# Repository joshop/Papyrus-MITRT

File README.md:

# Papyrus Avionics System
MIT Rocket Team Liquid Propulsion Avionics

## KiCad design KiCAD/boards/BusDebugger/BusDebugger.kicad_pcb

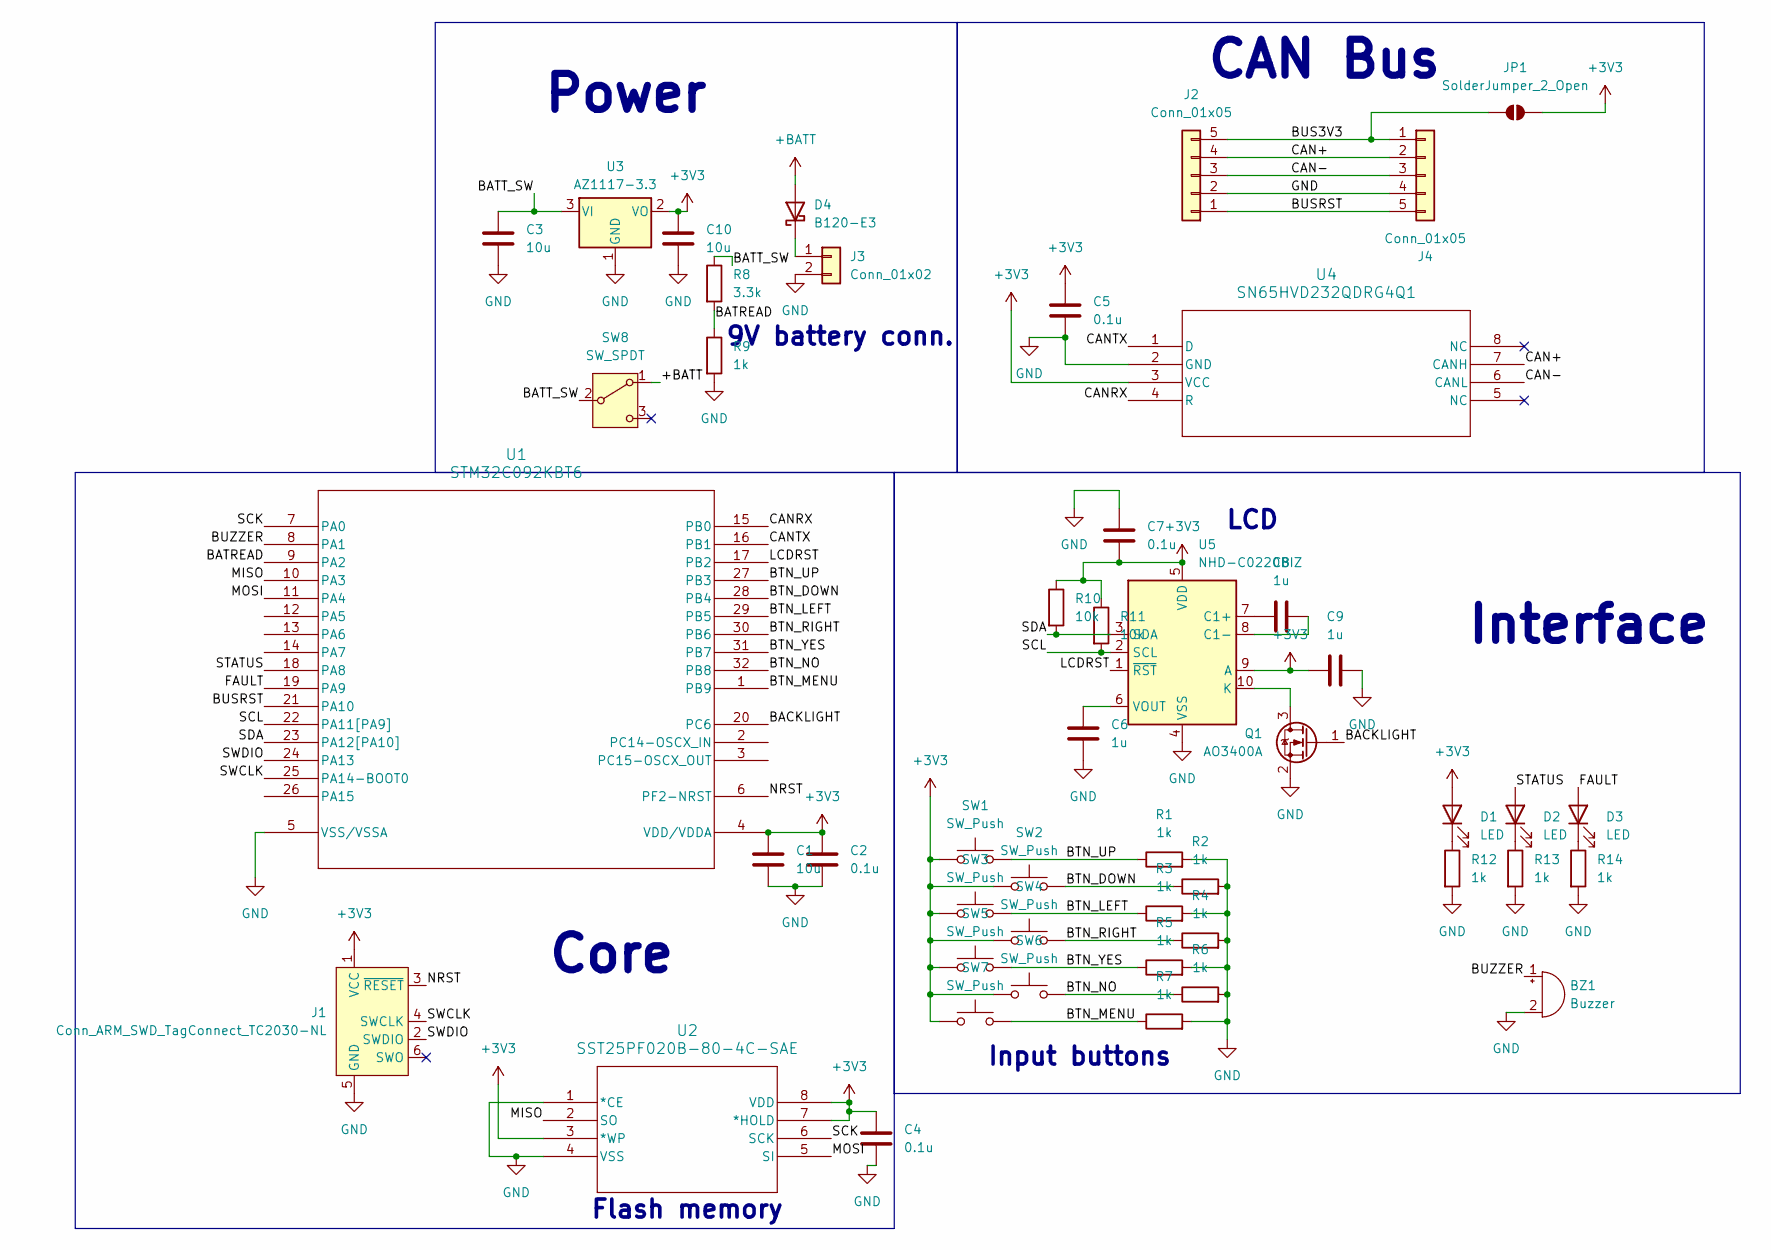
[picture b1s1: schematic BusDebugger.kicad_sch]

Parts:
BZ1: Buzzer; Buzzer_CUI_CPT-9019S-SMT
C1, C3, C10: 10u; C_0603_1608Metric
C2, C4, C5, C7: 0.1u; C_0603_1608Metric
C6, C8, C9: 1u; C_0603_1608Metric
D1, D2, D3: LED; D_0603_1608Metric
D4: B120-E3; D_SMA
J1: Conn_ARM_SWD_TagConnect_TC2030-NL; Tag-Connect_TC2030-IDC-NL_2x03_P1.27mm_Vertical
J2, J4: Conn_01x05; JST_XH_S5B-XH-A-1_1x05_P2.50mm_Horizontal
J3: Conn_01x02; PinHeader_1x02_P1.27mm_Vertical
JP1: SolderJumper_2_Open; SolderJumper-2_P1.3mm_Open_Pad1.0x1.5mm
Q1: AO3400A; SOT-23
R1, R2, R3, R4, R5, R6, R7, R9, R12, R13, R14: 1k; R_0603_1608Metric
R8: 3.3k; R_0603_1608Metric
R10, R11: 10k; R_0603_1608Metric
SW1, SW2, SW3, SW4, SW5, SW6, SW7: SW_Push; SW_Push_1P1T_NO_CK_KMR2
SW8: SW_SPDT; SW_Slide_SPDT_Straight_CK_OS102011MS2Q
U1: STM32C092KBT6; LQFP-32_STM
U2: SST25PF020B-80-4C-SAE; SOIC8_SA_SST_MCH
U3: AZ1117-3.3; SOT-223-3_TabPin2
U4: SN65HVD232QDRG4Q1; D8
U5: NHD-C0220BIZ; NHD-C0220BiZ

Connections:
+3V3: C1.1, C2.1, C4.1, C5.1, C7.2, C9.1, C10.1, D1.2 (A), J1.1 (VCC), JP1.2 (B), R10.1, R11.1, SW1.1, SW2.1, SW3.1, SW4.1, SW5.1, SW6.1, SW7.1, U1.4 (VDD/VDDA), U2.3 (*WP), U2.7 (*HOLD), U2.8 (VDD), U3.2 (VO), U4.3 (VCC), U5.5 (VDD), U5.9 (A)
+BATT: D4.2 (A), SW8.1 (A)
/BACKLIGHT: Q1.1 (G), U1.20 (PC6)
/BATREAD: R8.2, R9.1, U1.9 (PA2)
/BATT_SW: C3.1, R8.1, SW8.2 (B), U3.3 (VI)
/BTN_DOWN: R2.1, SW2.2, U1.28 (PB4)
/BTN_LEFT: R3.1, SW3.2, U1.29 (PB5)
/BTN_MENU: R7.1, SW7.2, U1.1 (PB9)
/BTN_NO: R6.1, SW6.2, U1.32 (PB8)
/BTN_RIGHT: R4.1, SW4.2, U1.30 (PB6)
/BTN_UP: R1.1, SW1.2, U1.27 (PB3)
/BTN_YES: R5.1, SW5.2, U1.31 (PB7)
/BUS3V3: J2.5, J4.1, JP1.1 (A)
/BUSRST: J2.1, J4.5, U1.21 (PA10)
/BUZZER: BZ1.1 (+), U1.8 (PA1)
/CAN+: J2.4, J4.2, U4.7 (CANH)
/CAN-: J2.3, J4.3, U4.6 (CANL)
/CANRX: U1.15 (PB0), U4.4 (R)
/CANTX: U1.16 (PB1), U4.1 (D)
/FAULT: D3.2 (A), U1.19 (PA9)
/LCDRST: U1.17 (PB2), U5.1 (~RST)
/MISO: U1.10 (PA3), U2.2 (SO)
/MOSI: U1.11 (PA4), U2.5 (SI)
/NRST: J1.3 (~RESET), U1.6 (PF2-NRST)
/SCK: U1.7 (PA0), U2.6 (SCK)
/SCL: R11.2, U1.22 (PA11[PA9]), U5.2 (SCL)
/SDA: R10.2, U1.23 (PA12[PA10]), U5.3 (SDA)
/STATUS: D2.2 (A), U1.18 (PA8)
/SWCLK: J1.4 (SWCLK), U1.25 (PA14-BOOT0)
/SWDIO: J1.2 (SWDIO), U1.24 (PA13)
GND: BZ1.2 (-), C1.2, C2.2, C3.2, C4.2, C5.2, C6.2, C7.1, C9.2, C10.2, J1.5 (GND), J2.2, J3.2, J4.4, Q1.2 (S), R1.2, R2.2, R3.2, R4.2, R5.2, R6.2, R7.2, R9.2, R12.2, R13.2, R14.2, U1.5 (VSS/VSSA), U2.1 (*CE), U2.4 (VSS), U3.1 (GND), U4.2 (GND), U5.4 (VSS)
unnamed: D1.1 (K), R12.1
unnamed: D2.1 (K), R13.1
unnamed: D3.1 (K), R14.1
unnamed: D4.1 (K), J3.1
unnamed: Q1.3 (D), U5.10 (K)
unnamed: C8.1, U5.7 (C1+)
unnamed: C8.2, U5.8 (C1-)
unnamed: C6.1, U5.6 (VOUT)

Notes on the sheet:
Core
CAN Bus
9V battery conn.
Power
Interface
LCD
Input buttons
Flash memory

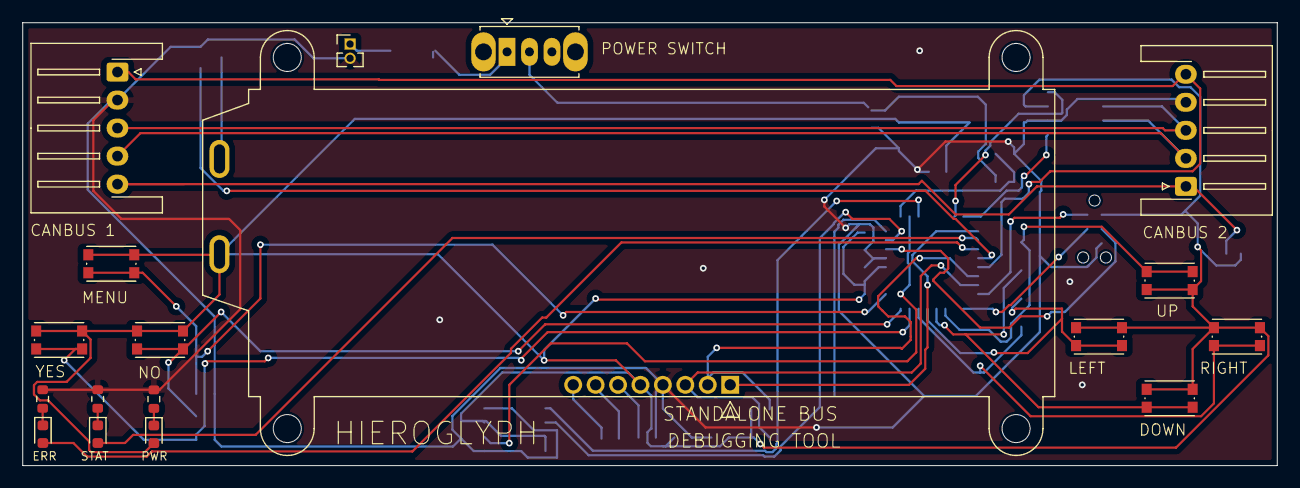
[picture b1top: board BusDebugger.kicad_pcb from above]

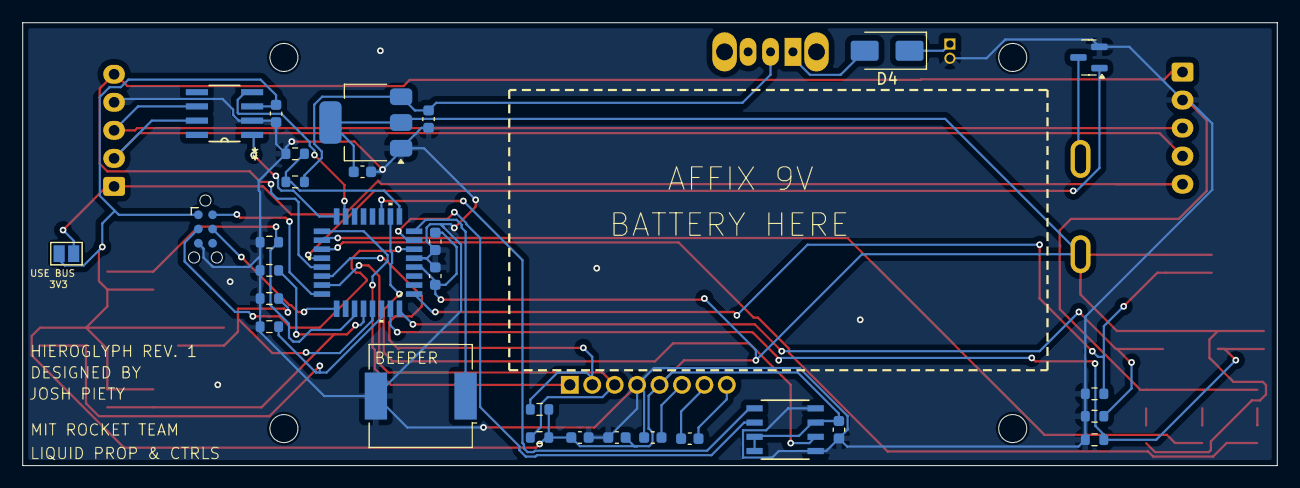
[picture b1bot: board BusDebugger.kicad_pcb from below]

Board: 2 copper layers, 111.9 x 39.5 mm, 48 parts (30 on the bottom side), 39 nets.

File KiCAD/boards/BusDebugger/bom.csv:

"Id";"Designator";"Footprint";"Quantity";"Designation";"Supplier and ref";
1;"D4";"D_SMA";1;"B120-E3";;;
2;"C10,C3,C1";"C_0603_1608Metric";3;"10u";;;
3;"J2,J4";"JST_XH_S5B-XH-A-1_1x05_P2.50mm_Horizontal";2;"Conn_01x05";;;
5;"R13,R14,R12,R3,R5,R9,R2,R4,R7,R6,R1";"R_0603_1608Metric";11;"1k";;;
6;"D1,D2,D3";"D_0603_1608Metric";3;"LED";;;
7;"SW8";"SW_Slide_SPDT_Straight_CK_OS102011MS2Q";1;"SW_SPDT";;;
8;"SW1,SW4,SW7,SW2,SW6,SW3,SW5";"SW_Push_1P1T_NO_CK_KMR2";7;"SW_Push";;;
9;"U5";"NHD-C0220BiZ";1;"NHD-C0220BIZ";;;
10;"R11,R10";"R_0603_1608Metric";2;"10k";;;
11;"C2,C4,C5,C7";"C_0603_1608Metric";4;"0.1u";;;
12;"BZ1";"Buzzer_CUI_CPT-9019S-SMT";1;"Buzzer";;;
13;"C6,C9,C8";"C_0603_1608Metric";3;"1u";;;
14;"U4";"D8";1;"SN65HVD232QDRG4Q1";;;
15;"U1";"LQFP-32_STM";1;"STM32C092KBT6";;;
16;"U3";"SOT-223-3_TabPin2";1;"AZ1117-3.3";;;
17;"R8";"R_0603_1608Metric";1;"3.3k";;;
18;"U2";"SOIC8_SA_SST_MCH";1;"SST25PF020B-80-4C-SAE";;;
19;"Q1";"SOT-23";1;"AO3400A";;;

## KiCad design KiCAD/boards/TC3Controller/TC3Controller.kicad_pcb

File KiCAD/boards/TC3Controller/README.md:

# TC3Controller
This is a controller board for three K-type thermocouples. In addition to the standard components, it contains:
- three MAX31855KASA thermocouple amplifiers
- optional filtering capacitors on thermocouple inputs
- three 2-terminal 2.54mm pitch screw terminals for thermocouples
- STATUS and FAULT LEDs
The board itself is 35.0mm x 37.3mm and uses M2 mounting holes.

We considered designing our own thermocouple amplifier to save cost, but decided not to. If necessary, this could be implemented as follows:
- Using a low noise amplifier such as the LMP7716MMX/NOPB (dual), produce a desired gain with feedback.
- Use another amplifier device, likely in the same dual package, to buffer a resistor divider and offset the voltage to allow reading of temperatures below the cold junction temperature.
- Separately, connect a temperature sensor such as the TMP126EDBVRQ1 and perform cold junction compensation in software.
Cold junction compensators and buffers could be reused between individual thermocouples.

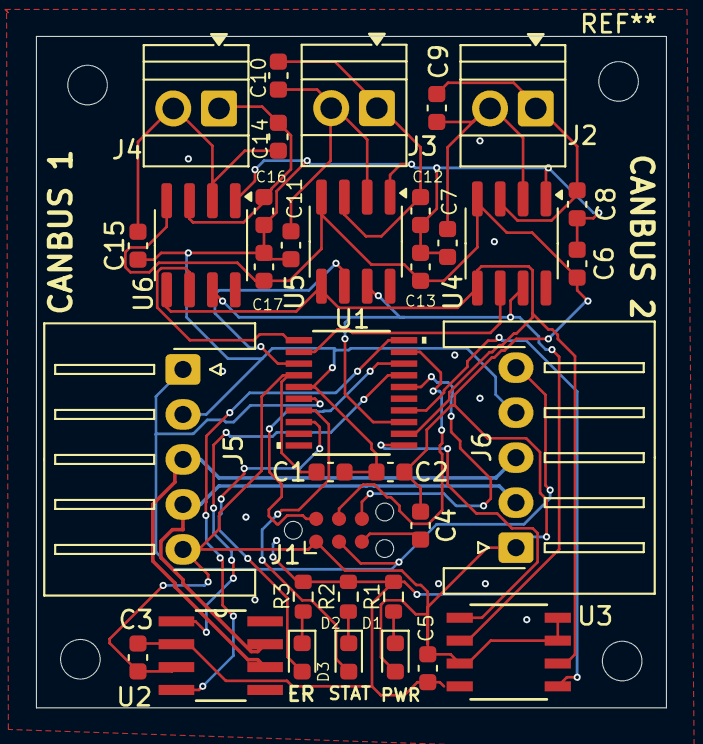
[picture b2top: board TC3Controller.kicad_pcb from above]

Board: 2 copper layers, 35.0 x 37.3 mm, 35 parts (0 on the bottom side), 28 nets.

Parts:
C1, C3, C4, C5, C6, C7, C8, C9, C10, C11, C12, C13, C14, C15, C16, C17: 100n; C_0603_1608Metric
C2: 10u; C_0603_1608Metric
D1, D2, D3: LED; LED_0603_1608Metric
J1: Conn_ARM_SWD_TagConnect_TC2030-NL; Tag-Connect_TC2030-IDC-NL_2x03_P1.27mm_Vertical
J2, J3, J4: Screw_Terminal_01x02; TerminalBlock_Xinya_XY308-2.54-2P_1x02_P2.54mm_Horizontal
J5, J6: Conn_01x05; JST_XH_S5B-XH-A-1_1x05_P2.50mm_Horizontal
R1, R2, R3: 1k; R_0603_1608Metric
U1: STM32C092FCP6; TSSOP20_STM
U2: SN65HVD232QDRG4Q1; D8
U3: SST25PF020B-80-4C-SAE; SOIC8_SA_SST_MCH
U4, U5, U6: MAX31855KASA; SOIC-8_3.9x4.9mm_P1.27mm

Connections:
+3V3: C1.1, C2.1, C3.1, C4.1, C5.1, C6.1, C13.1, C17.1, D1.2 (A), J1.1 (VCC), J5.5, J6.1, U1.4 (VDD/VDDA), U2.3 (VCC), U3.3 (*WP), U3.7 (*HOLD), U3.8 (VDD), U4.4 (V_{CC}), U5.4 (V_{CC}), U6.4 (V_{CC})
/CAN+: J5.4, J6.2, U2.7 (CANH)
/CAN-: J5.3, J6.3, U2.6 (CANL)
/CANRX: U1.20 (PB3/PB4/PB5/PB6), U2.4 (R)
/CANTX: U1.17 (PA12[PA10]), U2.1 (D)
/FAULT: D3.2 (A), U1.8 (PA1)
/FLASH_CE: U1.11 (PA4), U3.1 (*CE)
/MISO: U1.13 (PA6), U3.2 (SO), U4.7 (SO), U5.7 (SO), U6.7 (SO)
/MOSI: U1.14 (PA7), U3.5 (SI)
/RESETB: J1.3 (~RESET), J5.1, J6.5, U1.6 (PF2-NRST)
/SCK: U1.12 (PA5), U3.6 (SCK), U4.5 (SCK), U5.5 (SCK), U6.5 (SCK)
/STATUS: D2.2 (A), U1.7 (PA0)
/SWCLK: J1.4 (SWCLK), U1.19 (PA14-BOOT0/PA15)
/SWDIO: J1.2 (SWDIO), U1.18 (PA13)
/SWO: J1.6 (SWO), U1.16 (PA11[PA9])
/TC1_CS: U1.1 (PB7/PB8), U6.6 (~CS)
/TC2_CS: U1.2 (PC14-OSCX_IN), U4.6 (~CS)
/TC3_CS: U1.3 (PC15-OSCX_OUT), U5.6 (~CS)
GND: C1.2, C2.2, C3.2, C4.2, C5.2, C6.2, C7.2, C8.1, C11.2, C12.1, C13.2, C15.2, C16.1, C17.2, J1.5 (GND), J5.2, J6.4, R1.2, R2.2, R3.2, U1.5 (VSS/VSSA), U2.2 (GND), U3.4 (VSS), U4.1 (GND), U5.1 (GND), U6.1 (GND)
unnamed: D1.1 (K), R1.1
unnamed: D2.1 (K), R2.1
unnamed: D3.1 (K), R3.1
unnamed: C8.2, C9.1, J2.1, U4.3 (T+)
unnamed: C7.1, C9.2, J2.2, U4.2 (T-)
unnamed: C10.1, C12.2, J3.1, U5.3 (T+)
unnamed: C10.2, C11.1, J3.2, U5.2 (T-)
unnamed: C14.1, C16.2, J4.1, U6.3 (T+)
unnamed: C14.2, C15.1, J4.2, U6.2 (T-)

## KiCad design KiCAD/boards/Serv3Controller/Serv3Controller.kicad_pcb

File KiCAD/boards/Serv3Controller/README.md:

# Serv3Controller
This is a controller board for three servo motors. In addition to the standard components, it contains:
- three IRLML6344TRPBF N-channel MOSFETs for switching servo power
- STATUS LEDs for each servo to indicate both power and fault conditions
- two 2-terminal 2.54mm pitch screw terminals for servo voltage (5V or greater)
- 33mohm current sense resistors on each servo to detect stall conditions
- three standard 2.54mm male pin headers to connect to servos
The board itself is 42.4mm x 29.6mm and uses M2 mounting holes.

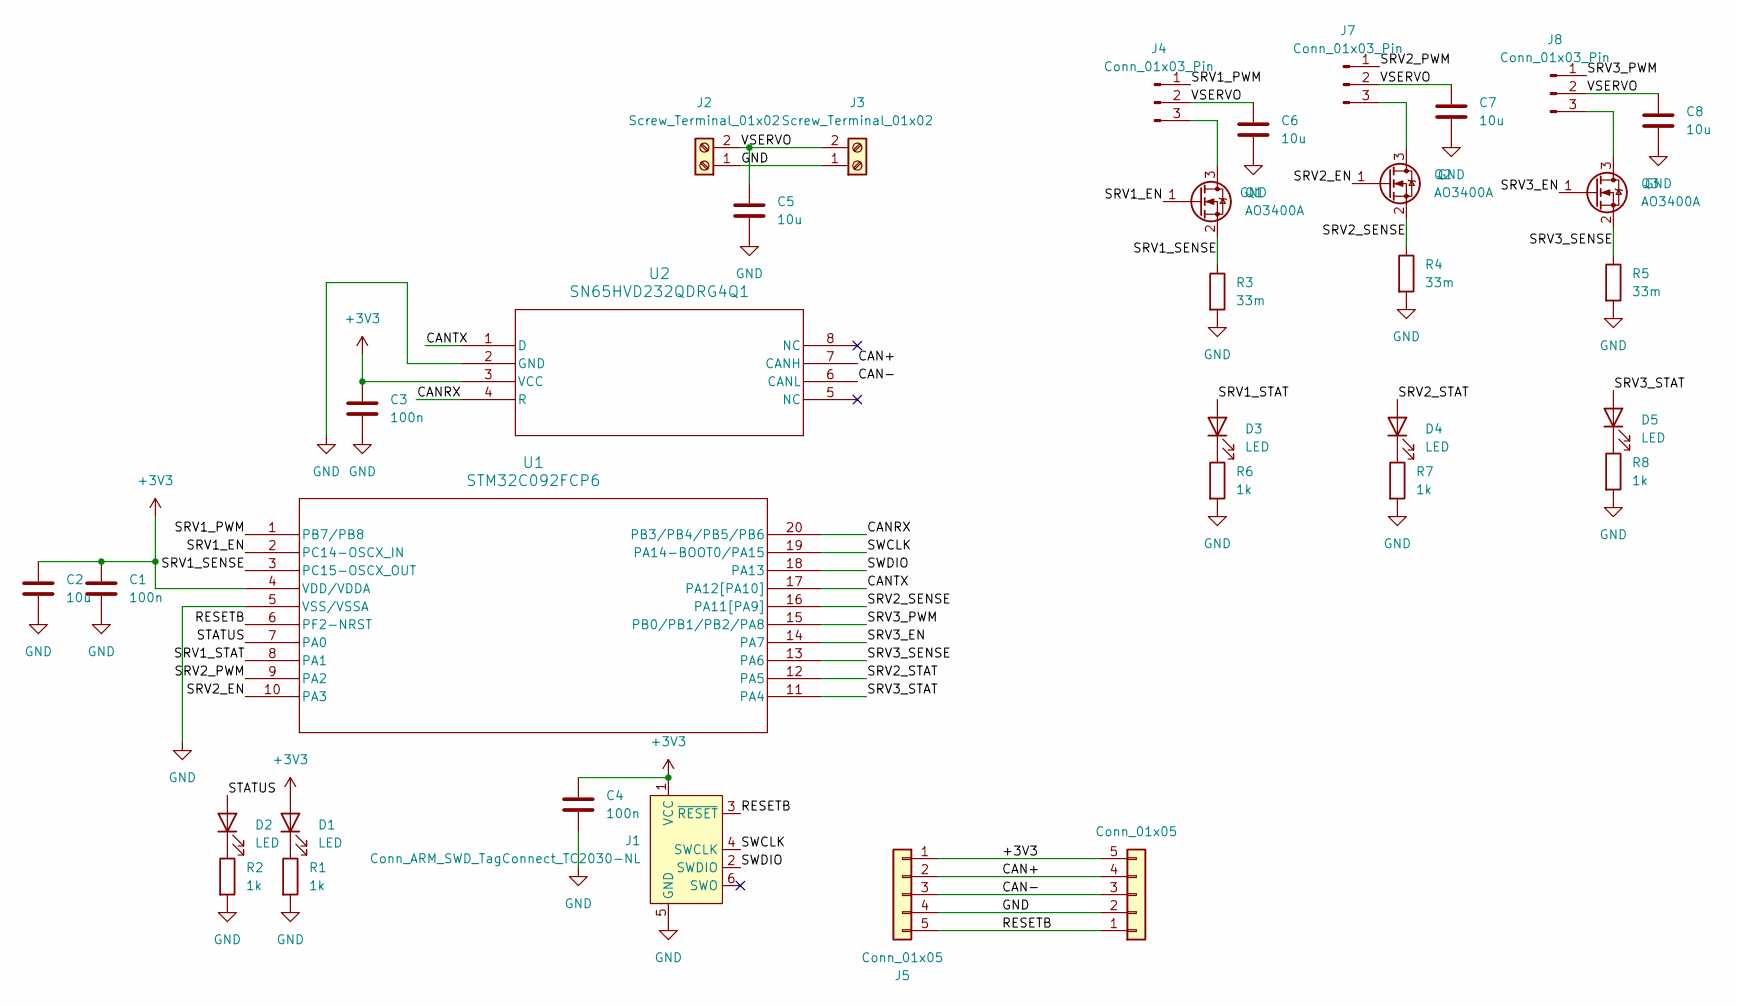
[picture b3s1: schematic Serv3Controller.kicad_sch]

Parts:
C1, C3, C4: 100n; C_0603_1608Metric
C2, C5, C6, C7, C8: 10u; C_0603_1608Metric
D1, D2, D3, D4, D5: LED; LED_0603_1608Metric
J1: Conn_ARM_SWD_TagConnect_TC2030-NL; Tag-Connect_TC2030-IDC-NL_2x03_P1.27mm_Vertical
J2, J3: Screw_Terminal_01x02; TerminalBlock_Xinya_XY308-2.54-2P_1x02_P2.54mm_Horizontal
J4, J7, J8: Conn_01x03_Pin; PinHeader_1x03_P2.54mm_Vertical
J5, J6: Conn_01x05; JST_XH_S5B-XH-A-1_1x05_P2.50mm_Horizontal
Q1, Q2, Q3: AO3400A; SOT-23
R1, R2, R6, R7, R8: 1k; R_0603_1608Metric
R3, R4, R5: 33m; R_0603_1608Metric
U1: STM32C092FCP6; TSSOP20_STM
U2: SN65HVD232QDRG4Q1; D8

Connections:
+3V3: C1.1, C2.1, C3.1, C4.1, D1.2 (A), J1.1 (VCC), J5.1, J6.5, U1.4 (VDD/VDDA), U2.3 (VCC)
/CAN+: J5.2, J6.4, U2.7 (CANH)
/CAN-: J5.3, J6.3, U2.6 (CANL)
/CANRX: U1.20 (PB3/PB4/PB5/PB6), U2.4 (R)
/CANTX: U1.17 (PA12[PA10]), U2.1 (D)
/RESETB: J1.3 (~RESET), J5.5, J6.1, U1.6 (PF2-NRST)
/SRV1_EN: Q1.1 (G), U1.2 (PC14-OSCX_IN)
/SRV1_PWM: J4.1, U1.1 (PB7/PB8)
/SRV1_SENSE: Q1.2 (S), R3.1, U1.3 (PC15-OSCX_OUT)
/SRV1_STAT: D3.2 (A), U1.8 (PA1)
/SRV2_EN: Q2.1 (G), U1.10 (PA3)
/SRV2_PWM: J7.1, U1.9 (PA2)
/SRV2_SENSE: Q2.2 (S), R4.1, U1.16 (PA11[PA9])
/SRV2_STAT: D4.2 (A), U1.12 (PA5)
/SRV3_EN: Q3.1 (G), U1.14 (PA7)
/SRV3_PWM: J8.1, U1.15 (PB0/PB1/PB2/PA8)
/SRV3_SENSE: Q3.2 (S), R5.1, U1.13 (PA6)
/SRV3_STAT: D5.2 (A), U1.11 (PA4)
/STATUS: D2.2 (A), U1.7 (PA0)
/SWCLK: J1.4 (SWCLK), U1.19 (PA14-BOOT0/PA15)
/SWDIO: J1.2 (SWDIO), U1.18 (PA13)
/VSERVO: C5.1, C6.1, C7.1, C8.1, J2.2, J3.2, J4.2, J7.2, J8.2
GND: C1.2, C2.2, C3.2, C4.2, C5.2, C6.2, C7.2, C8.2, J1.5 (GND), J2.1, J3.1, J5.4, J6.2, R1.2, R2.2, R3.2, R4.2, R5.2, R6.2, R7.2, R8.2, U1.5 (VSS/VSSA), U2.2 (GND)
unnamed: D1.1 (K), R1.1
unnamed: D2.1 (K), R2.1
unnamed: D3.1 (K), R6.1
unnamed: D4.1 (K), R7.1
unnamed: D5.1 (K), R8.1
unnamed: J4.3, Q1.3 (D)
unnamed: J7.3, Q2.3 (D)
unnamed: J8.3, Q3.3 (D)

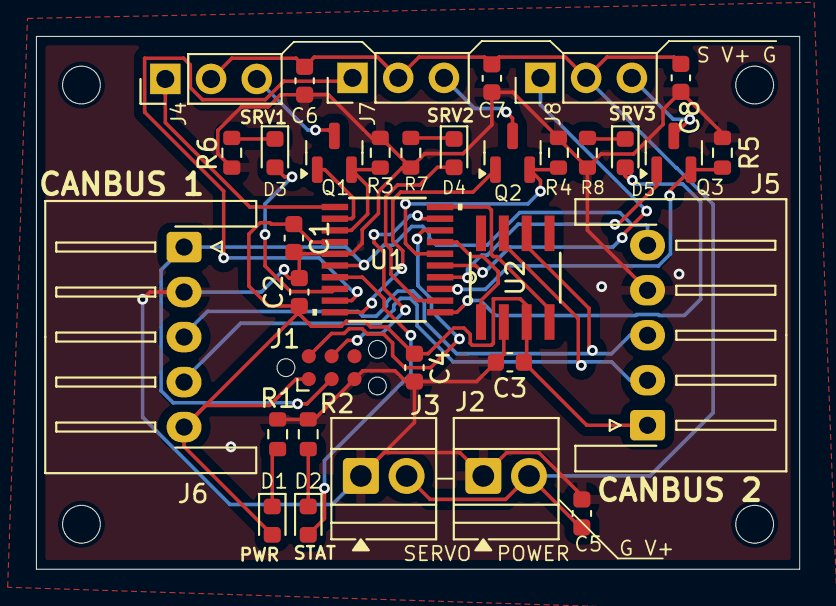
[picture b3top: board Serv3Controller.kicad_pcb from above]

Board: 2 copper layers, 42.4 x 29.6 mm, 34 parts (0 on the bottom side), 31 nets.

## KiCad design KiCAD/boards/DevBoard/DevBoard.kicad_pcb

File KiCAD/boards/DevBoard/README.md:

# DevBoard
This is a test board for STM32C092 microcontroller and CAN bus. It contains the following components, common to most/all standard boards in the DAQ system:
- STM32C092FCP6 microcontroller, TSSOP-20 package with built in FDCAN
- SN65HVD232QDRG4Q1 CAN transceiver
- SST25PF020B-80-4C-SAE SPI flash memory
- Tag-Connect 6-pin programming header through SWD
All STM32 peripheral pins and the CAN bus are broken out to headers.

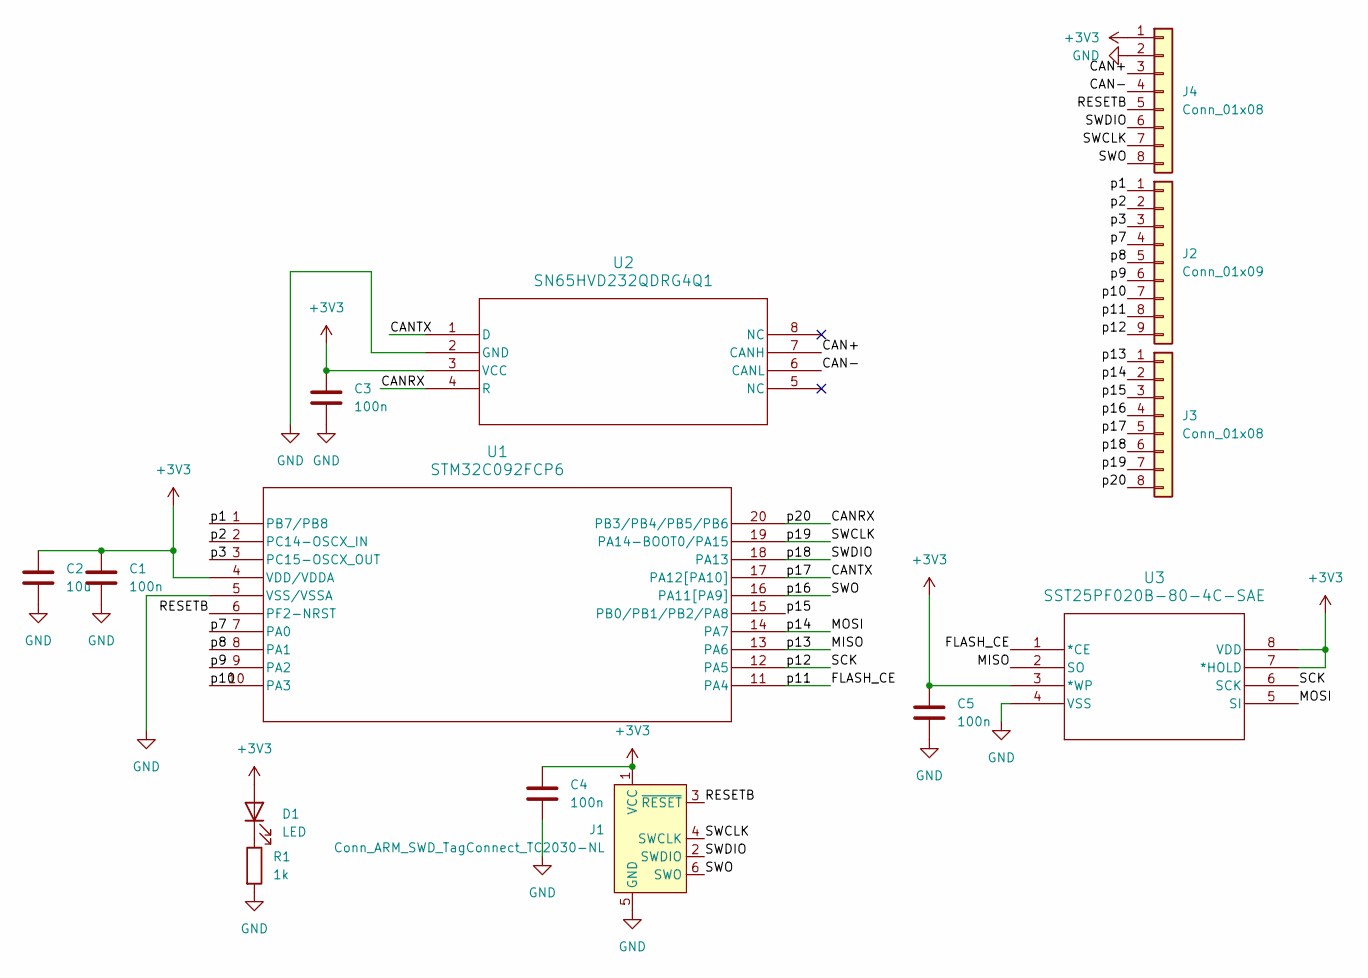
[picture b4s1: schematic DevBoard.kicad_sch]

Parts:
C1, C3, C4, C5: 100n; C_0603_1608Metric
C2: 10u; C_0603_1608Metric
D1: LED; LED_0603_1608Metric
J1: Conn_ARM_SWD_TagConnect_TC2030-NL; Tag-Connect_TC2030-IDC-NL_2x03_P1.27mm_Vertical
J2: Conn_01x09; PinSocket_1x09_P2.54mm_Vertical
J3, J4: Conn_01x08; PinSocket_1x08_P2.54mm_Vertical
R1: 1k; R_0603_1608Metric
U1: STM32C092FCP6; TSSOP20_STM
U2: SN65HVD232QDRG4Q1; D8
U3: SST25PF020B-80-4C-SAE; SOIC8_SA_SST_MCH

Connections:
+3V3: C1.1, C2.1, C3.1, C4.1, C5.1, D1.2 (A), J1.1 (VCC), J4.1, U1.4 (VDD/VDDA), U2.3 (VCC), U3.3 (*WP), U3.7 (*HOLD), U3.8 (VDD)
/CAN+: J4.3, U2.7 (CANH)
/CAN-: J4.4, U2.6 (CANL)
/CANRX: J3.8, U1.20 (PB3/PB4/PB5/PB6), U2.4 (R)
/CANTX: J3.5, U1.17 (PA12[PA10]), U2.1 (D)
/FLASH_CE: J2.8, U1.11 (PA4), U3.1 (*CE)
/MISO: J3.1, U1.13 (PA6), U3.2 (SO)
/MOSI: J3.2, U1.14 (PA7), U3.5 (SI)
/RESETB: J1.3 (~RESET), J4.5, U1.6 (PF2-NRST)
/SCK: J2.9, U1.12 (PA5), U3.6 (SCK)
/SWCLK: J1.4 (SWCLK), J3.7, J4.7, U1.19 (PA14-BOOT0/PA15)
/SWDIO: J1.2 (SWDIO), J3.6, J4.6, U1.18 (PA13)
/SWO: J1.6 (SWO), J3.4, J4.8, U1.16 (PA11[PA9])
/p1: J2.1, U1.1 (PB7/PB8)
/p2: J2.2, U1.2 (PC14-OSCX_IN)
/p3: J2.3, U1.3 (PC15-OSCX_OUT)
/p7: J2.4, U1.7 (PA0)
/p8: J2.5, U1.8 (PA1)
/p9: J2.6, U1.9 (PA2)
/p10: J2.7, U1.10 (PA3)
/p15: J3.3, U1.15 (PB0/PB1/PB2/PA8)
GND: C1.2, C2.2, C3.2, C4.2, C5.2, J1.5 (GND), J4.2, R1.2, U1.5 (VSS/VSSA), U2.2 (GND), U3.4 (VSS)
unnamed: D1.1 (K), R1.1

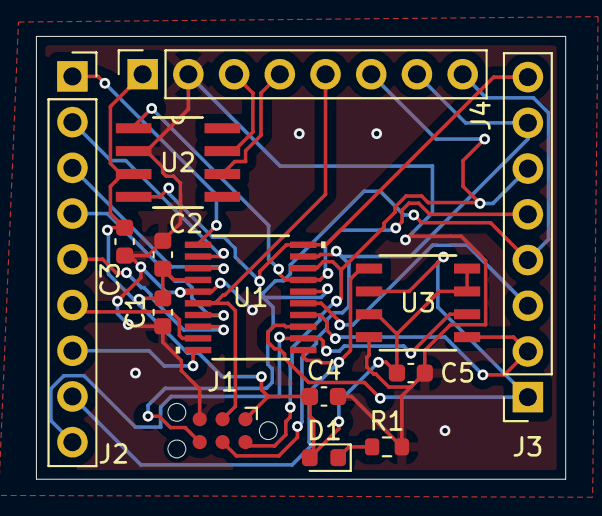
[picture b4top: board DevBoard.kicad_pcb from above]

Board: 2 copper layers, 29.4 x 24.6 mm, 14 parts (0 on the bottom side), 23 nets.

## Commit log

2025-06-11 Added some symbols/footprints and dev board schematic (NOT DONE YET)
2025-06-12 DevBoard first revision
2025-06-12 Final DevBoard PCB
2025-06-16 Thermocouple Board rev1
2025-06-16 Basic documentation
2025-07-01 Servo controller board & fixes to TC board
2025-07-01 Add README for Serv3Controller
2025-07-24 Bus debugger & some board tweaks
